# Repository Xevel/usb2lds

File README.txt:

USB2LDS
=======

2014 Nicolas "Xevel" Saugnier

Interface boards for the Neato LDS - the Lidar of the XV-11.
More on the Neato LDS : http://xv11hacking.wikispaces.com/LIDAR+Sensor

Boards:
- USB2LDS: USB interface for the Neato LDS, that also takes care of the motor control.
- Neato LDS Breakout Board (or NLDSBB): Simple breakout board that exposes the UART of the LDS, but takes care of the motor control.

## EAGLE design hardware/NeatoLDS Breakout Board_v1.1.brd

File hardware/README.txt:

USB2LDS hardware
================

USB2LDS versions:

v2.0 - 2014/01/12
- replaced FTDI with Atmega32u2
- added mosfet to allow PWM control of the motor
- added debug and hacking pads (/RST, /HWB, and the whole SPI bus)

v1.1 - 2014/01/11
- corrected LDS_TX/LDS_RX inversion on the connector
- The Lidar needs more power, use 3.3V regulator power instead of 3V3OUT from the FT232RL

V1.0 - 2014/01/09
- inital release

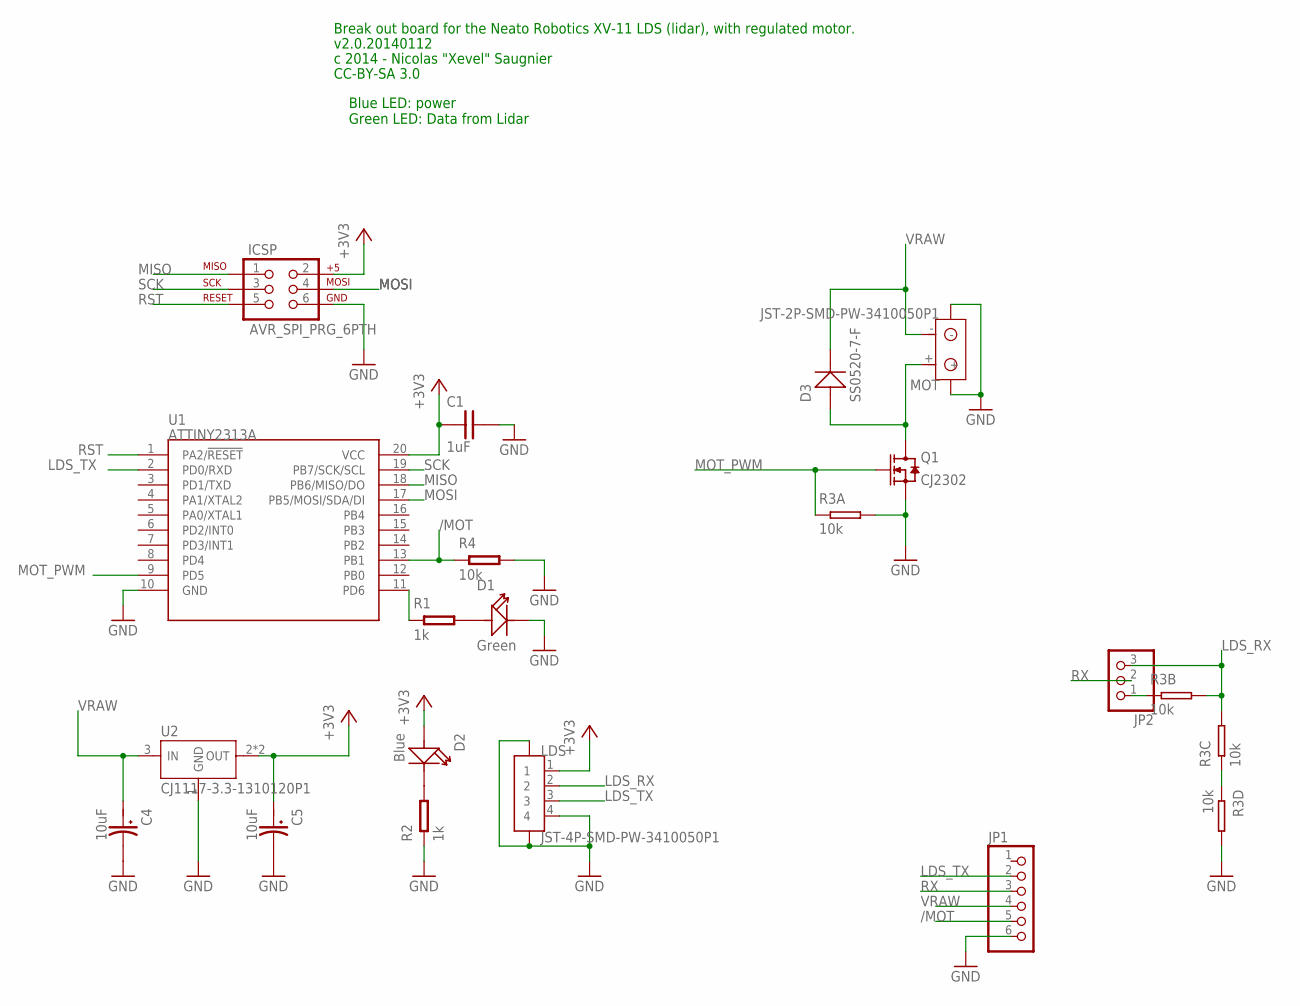
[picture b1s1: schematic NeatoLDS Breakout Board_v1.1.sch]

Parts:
C1: 1uF; C0603
C4, C5: 10uF; AVX-A
D1: Green; LED0603
D2: Blue; LED0603
D3: SS0520-7-F; SOD123
ICSP: AVR_SPI_PRG_6PTH; 2X3
JP1: PINHD-1X6; 1X06
JP2: PINHD-1X3; 1X03
LDS: JST-4P-SMD-PW-3410050P1; CON-4P-SMD-2.0-90D
MOT: JST-2P-SMD-PW-3410050P1; 2P-SMD-2.0-90D
Q1: CJ2302; SOT23
R1, R2: 1k; R0603
R3: 10k; R1206-8
R4: 10k; R0603
U1: ATTINY2313A; SOP20W
U2: CJ1117-3.3-1310120P1; SOT89

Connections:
+3V3: C1.1, C5.+ (1), D2.+, ICSP.2, LDS.1, U1.20 (VCC), U2.2 (OUT), U2.4 (OUT)
/MOT: JP1.5, R4.1, U1.13 (PB1)
GND: C1.2, C4.- (2), C5.- (2), D1.-, ICSP.6, JP1.6, LDS.4, LDS.5, LDS.6, MOT.3, MOT.4, Q1.2 (S), R2.1, R3.5 (2), R3.8 (2), R4.2, U1.10 (GND), U2.1 (GND)
LDS_RX: JP2.3, LDS.2, R3.6 (2), R3.7 (2)
LDS_TX: JP1.2, LDS.3, U1.2 (PD0/RXD)
MISO: ICSP.1, U1.18 (PB6/MISO/DO)
MOSI: ICSP.4, U1.17 (PB5/MOSI/SDA/DI)
MOT_PWM: Q1.1 (G), R3.1, U1.9 (PD5)
unnamed: R3.3 (1), R3.4 (1)
unnamed: JP2.1, R3.2 (1)
unnamed: R1.1, U1.11 (PD6)
unnamed: D3.+, MOT.+, Q1.3 (D)
unnamed: D1.+, R1.2
unnamed: D2.-, R2.2
RST: ICSP.5, U1.1 (PA2/!RESET)
RX: JP1.3, JP2.2
SCK: ICSP.3, U1.19 (PB7/SCK/SCL)
VRAW: C4.+ (1), D3.-, JP1.4, MOT.-, U2.3 (IN)

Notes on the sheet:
Blue LED: power Green LED: Data from Lidar
Break out board for the Neato Robotics XV-11 LDS (lidar), with regulated motor.
c 2014 - Nicolas "Xevel" Saugnier
CC-BY-SA 3.0
v2.0.20140112

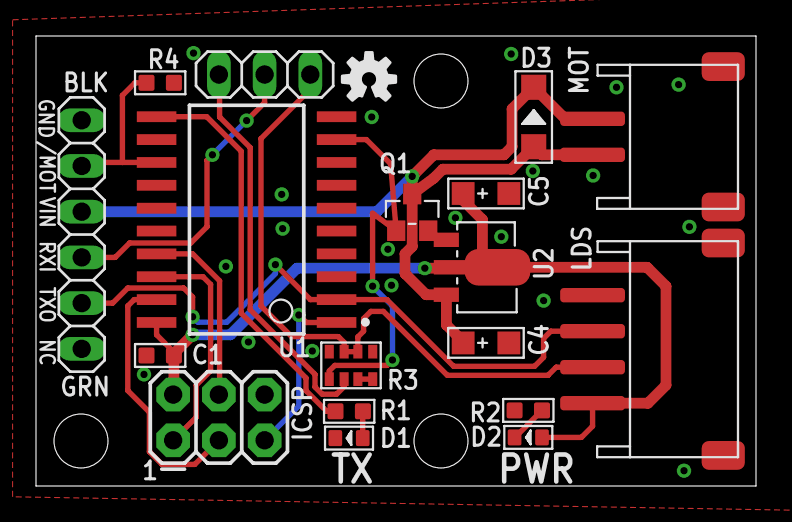
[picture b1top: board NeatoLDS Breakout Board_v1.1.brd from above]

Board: 2 copper layers, 40.0 x 25.0 mm, 20 parts (1 on the bottom side), 18 nets.

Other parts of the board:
U$1, U$2: OSHW-LOGO-S

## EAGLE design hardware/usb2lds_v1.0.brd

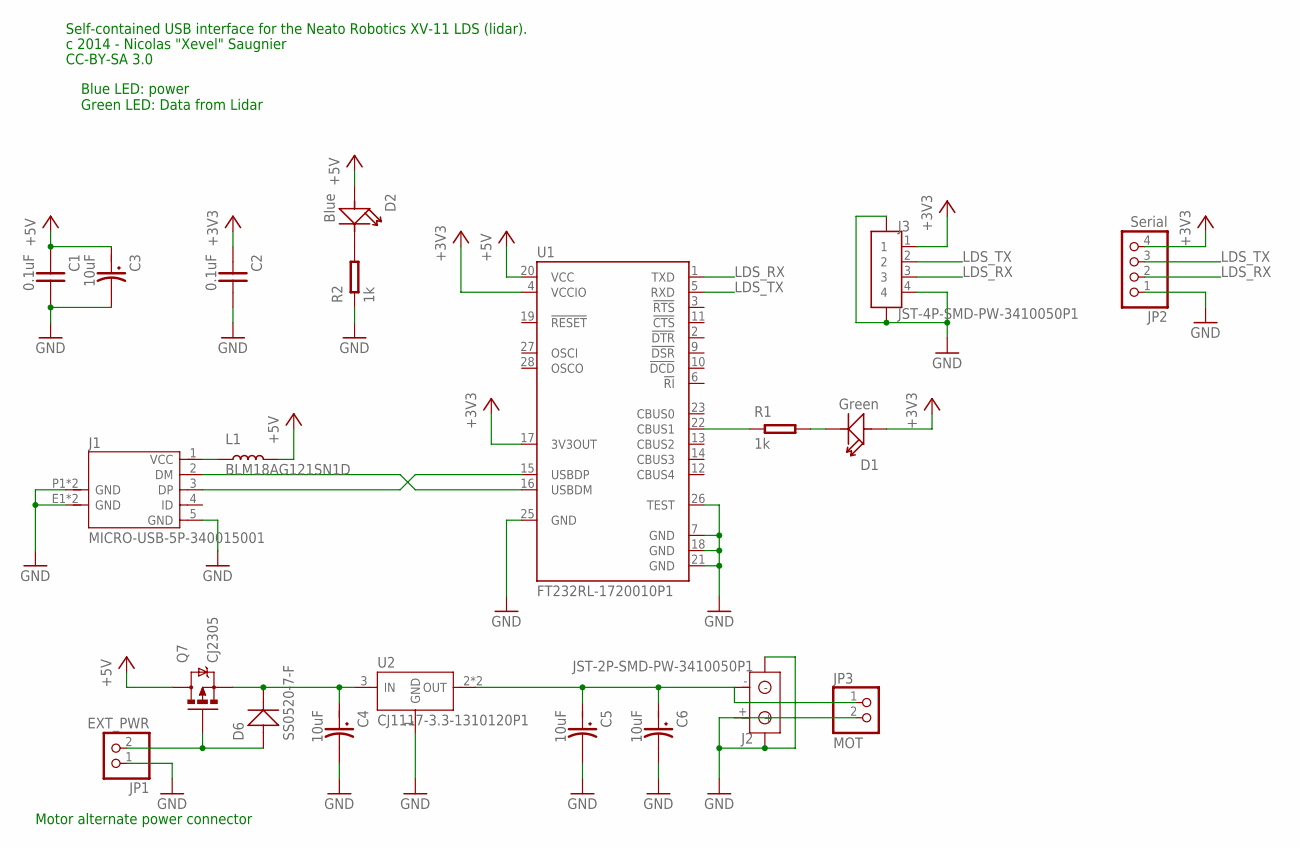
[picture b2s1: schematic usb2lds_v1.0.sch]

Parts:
C1, C2: 0.1uF; C0603
C3, C4, C5, C6: 10uF; AVX-A
D1: Green; LED0603
D2: Blue; LED0603
D6: SS0520-7-F; SOD123
J1: MICRO-USB-5P-340015001; B-SMD-5P
J2: JST-2P-SMD-PW-3410050P1; 2P-SMD-2.0-90D
J3: JST-4P-SMD-PW-3410050P1; CON-4P-SMD-2.0-90D
JP1: EXT_PWR; 1X02
JP2: Serial; 1X04
JP3: MOT; 1X02
L1: BLM18AG121SN1D; L0603
Q7: CJ2305; SOT-23-3_N/SSOT-3_N
R1, R2: 1k; R0603
U1: FT232RL-1720010P1; SSOP28
U2: CJ1117-3.3-1310120P1; SOT89

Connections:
+3V3: C2.1, D1.+, J3.1, JP2.4, U1.4 (VCCIO), U1.17 (3V3OUT)
+5V: C1.1, C3.+ (1), D2.+, L1.2, Q7.3 (D), U1.20 (VCC)
GND: C1.2, C2.2, C3.- (2), C4.- (2), C5.- (2), C6.- (2), J1.5 (GND), J1.E1 (GND), J1.E2 (GND), J1.P1 (GND), J1.P2 (GND), J2.3, J2.4, J2.+, J3.4, J3.5, J3.6, JP1.1, JP2.1, JP3.2, R2.1, U1.7 (GND), U1.18 (GND), U1.21 (GND), U1.25 (GND), U1.26 (TEST), U2.1 (GND)
LDS_RX: J3.3, JP2.2, U1.1 (TXD)
LDS_TX: J3.2, JP2.3, U1.5 (RXD)
unnamed: J1.2 (DM), U1.16 (USBDM)
unnamed: J1.3 (DP), U1.15 (USBDP)
unnamed: J1.1 (VCC), L1.1
unnamed: D1.-, R1.2
unnamed: D2.-, R2.2
unnamed: R1.1, U1.22 (CBUS1)
unnamed: C5.+ (1), C6.+ (1), J2.-, JP3.1, U2.2 (OUT), U2.4 (OUT)
unnamed: C4.+ (1), D6.-, Q7.2 (S), U2.3 (IN)
VUSB: D6.+, JP1.2, Q7.1 (G)

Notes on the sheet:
Blue LED: power Green LED: Data from Lidar
Self-contained USB interface for the Neato Robotics XV-11 LDS (lidar).
c 2014 - Nicolas "Xevel" Saugnier
CC-BY-SA 3.0
Motor alternate power connector

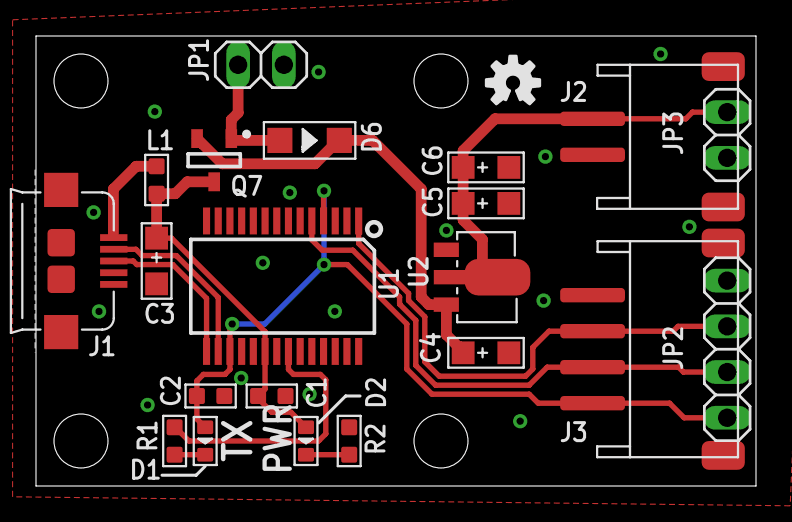
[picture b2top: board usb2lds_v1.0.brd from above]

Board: 2 copper layers, 40.0 x 25.0 mm, 23 parts (1 on the bottom side), 14 nets.

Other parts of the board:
U$1, U$2: OSHW-LOGO-S

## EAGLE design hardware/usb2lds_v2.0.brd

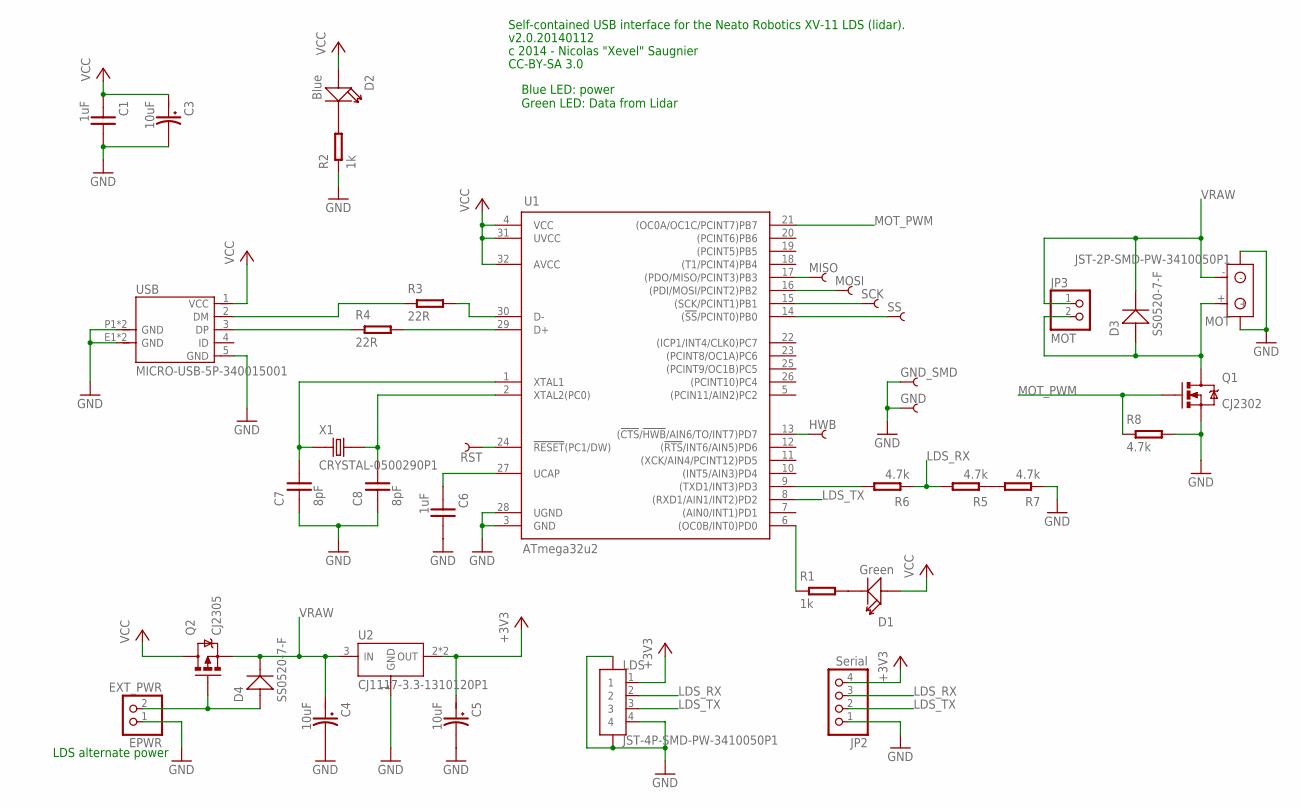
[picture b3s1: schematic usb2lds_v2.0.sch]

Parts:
C1, C6: 1uF; C0603
C3, C4, C5: 10uF; AVX-A
C7, C8: 8pF; C0603
D1: Green; LED0603
D2: Blue; LED0603
D3, D4: SS0520-7-F; SOD123
EPWR: EXT_PWR; 1X02
GND: PIN_SMD_2X2.5
GND_SMD: PIN_SMD_2X2.5
HWB: PIN_SMD_2X2.5
JP2: Serial; 1X04
JP3: MOT; 1X02
LDS: JST-4P-SMD-PW-3410050P1; CON-4P-SMD-2.0-90D
MISO: PIN_SMD_2X2.5
MOSI: PIN_SMD_2X2.5
MOT: JST-2P-SMD-PW-3410050P1; 2P-SMD-2.0-90D
Q1: CJ2302; SOT-23-3_N/SSOT-3_N
Q2: CJ2305; SOT-23-3_N/SSOT-3_N
R1, R2: 1k; R0603
R3, R4: 22R; R0603
R5, R6, R7, R8: 4.7k; R0603
RST: PIN_SMD_2X2.5
SCK: PIN_SMD_2X2.5
SS: PIN_SMD_2X2.5
U1: ATmega32u2; QFN-32_50P_L_MOD
U2: CJ1117-3.3-1310120P1; SOT89
USB: MICRO-USB-5P-340015001; B-SMD-5P
X1: CRYSTAL-0500290P1; 2P-SMD-5.0X3.2

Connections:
+3V3: C5.+ (1), JP2.4, LDS.1, U2.2 (OUT), U2.4 (OUT)
GND: C1.2, C3.- (2), C4.- (2), C5.- (2), C6.2, C7.1, C8.1, EPWR.1, GND.PIN, GND_SMD.PIN, JP2.1, LDS.4, LDS.5, LDS.6, MOT.3, MOT.4, Q1.2 (S), R2.1, R7.1, R8.2, U1.3 (GND), U1.28 (UGND), U2.1 (GND), USB.5 (GND), USB.E1 (GND), USB.E2 (GND), USB.P1 (GND), USB.P2 (GND)
HWB: HWB.PIN, U1.13 ((!CTS!/!HWB!/AIN6/TO/INT7)PD7)
LDS_RX: JP2.3, LDS.2, R5.2, R6.1
LDS_TX: JP2.2, LDS.3, U1.8 ((RXD1/AIN1/INT2)PD2)
MOT_PWM: Q1.1 (G), R8.1, U1.21 ((OC0A/OC1C/PCINT7)PB7)
unnamed: R6.2, U1.9 ((TXD1/INT3)PD3)
unnamed: R1.1, U1.6 ((OC0B/INT0)PD0)
unnamed: C6.1, U1.27 (UCAP)
unnamed: D3.+, JP3.2, MOT.+, Q1.3 (D)
unnamed: C8.2, U1.2 (XTAL2(PC0)), X1.2
unnamed: D1.-, R1.2
unnamed: D2.-, R2.2
unnamed: C7.2, U1.1 (XTAL1), X1.1
unnamed: R5.1, R7.2
unnamed: R3.2, U1.30 (D-)
unnamed: R4.2, U1.29 (D+)
unnamed: R3.1, USB.2 (DM)
unnamed: R4.1, USB.3 (DP)
unnamed: MISO.PIN, U1.17 ((PDO/MISO/PCINT3)PB3)
unnamed: MOSI.PIN, U1.16 ((PDI/MOSI/PCINT2)PB2)
unnamed: SCK.PIN, U1.15 ((SCK/PCINT1)PB1)
unnamed: SS.PIN, U1.14 ((!SS!/PCINT0)PB0)
RST: RST.PIN, U1.24 (!RESET!(PC1/DW))
VCC: C1.1, C3.+ (1), D1.+, D2.+, Q2.3 (D), U1.4 (VCC), U1.31 (UVCC), U1.32 (AVCC), USB.1 (VCC)
VRAW: C4.+ (1), D3.-, D4.-, JP3.1, MOT.-, Q2.2 (S), U2.3 (IN)
VUSB: D4.+, EPWR.2, Q2.1 (G)

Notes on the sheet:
Blue LED: power Green LED: Data from Lidar
Self-contained USB interface for the Neato Robotics XV-11 LDS (lidar).
c 2014 - Nicolas "Xevel" Saugnier
CC-BY-SA 3.0
LDS alternate power
v2.0.20140112

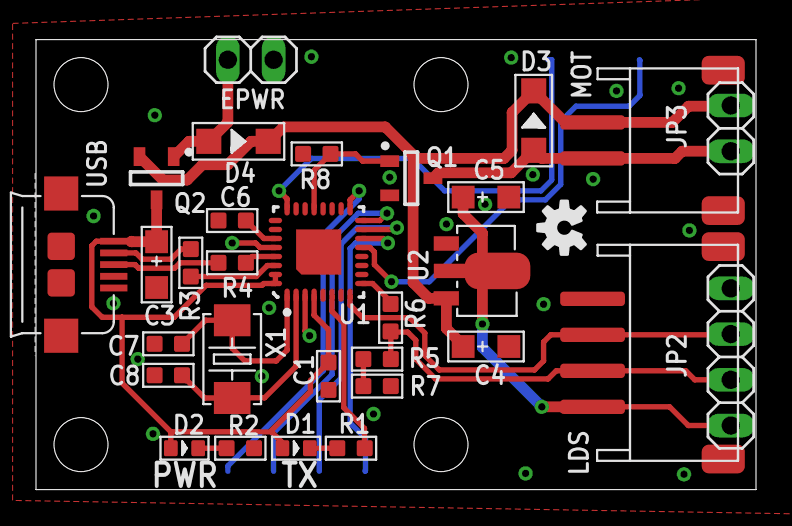
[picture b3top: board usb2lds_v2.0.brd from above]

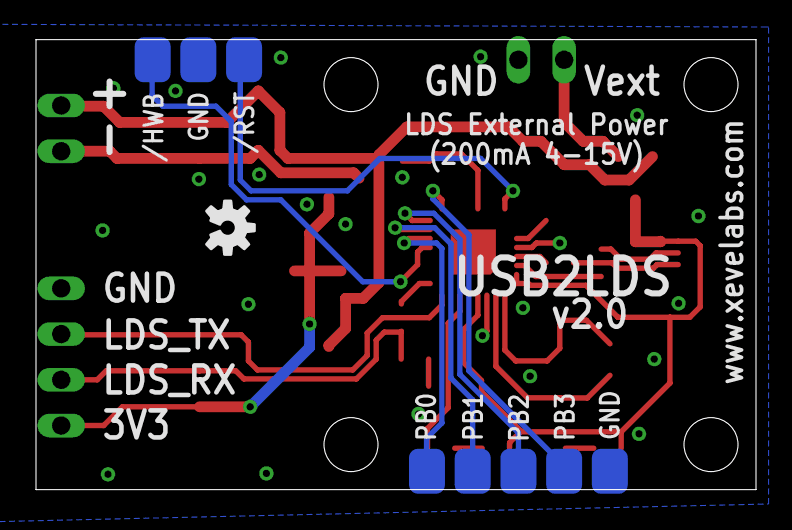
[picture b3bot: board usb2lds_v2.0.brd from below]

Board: 2 copper layers, 40.0 x 25.0 mm, 40 parts (9 on the bottom side), 27 nets.

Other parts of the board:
U$1, U$2: OSHW-LOGO-S

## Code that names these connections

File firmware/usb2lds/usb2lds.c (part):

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#include "time.h"

// Pin wired:
//   USART RX   (PD2/RXD1)
//   USART TX   (PD3/TXD1)
//   MOT PWM    (PB7/OC0A) inverted logic
//   TX LED     (PD0)
//   MISO       PB3
//   MOSI       PB2
//   SCK        PB1
//   !SS        PB0


USB_ClassInfo_CDC_Device_t VirtualSerial_CDC_Interface =
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}

void motor_init(){
    // Setup motor PWM (PD5/OC0B), inverting logic, phase correct (mode 1)
    TCCR0A = (1 << COM0A1) | (0 << COM0A0) | (0 << WGM01) | (1 << WGM00);
    TCCR0B = (0 << WGM02) | (1 << CS02) | (0 << CS01) | (0 << CS00);
    apply_motor_pwm(0);
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
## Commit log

2014-03-07 Initial import, with USB2LDS boards, NLDSBB boards and preliminary code for the NLDSBB.
2014-03-07 Basic firmware tree. Some more rework of the arch to come.
2014-03-07 Added a lib for LDS parsing. There are two proj to cater to different arch.
2014-03-07 Doc, license.
2014-03-07 Frankenstein-style usb2lds firmware, out of LUFA USBtoSerial, nldsbb and usb2ax. Not finished (motor control needed) and not tested at all.
2014-03-09 Added motor control and setup mode to tune the PID and more.
2014-03-09 Added a command to jumpstart the motor in case it has been stopped. Stopp the motor when going for a Reset.
2014-06-21 Set better PID values by default. Added 9600 bps for the setup mode.

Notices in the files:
firmware/usb2lds/usb2lds.c:
Copyright 2014 - Nicolas "Xevel" Saugnier
Original notice:
Copyright 2013  Dean Camera (dean [at] fourwalledcubicle [dot] com)
parts and their libraries:
SparkFun-Aesthetics: Licensing: CC v3.0 Share-Alike You are welcome to use this library for commercial purposes.
